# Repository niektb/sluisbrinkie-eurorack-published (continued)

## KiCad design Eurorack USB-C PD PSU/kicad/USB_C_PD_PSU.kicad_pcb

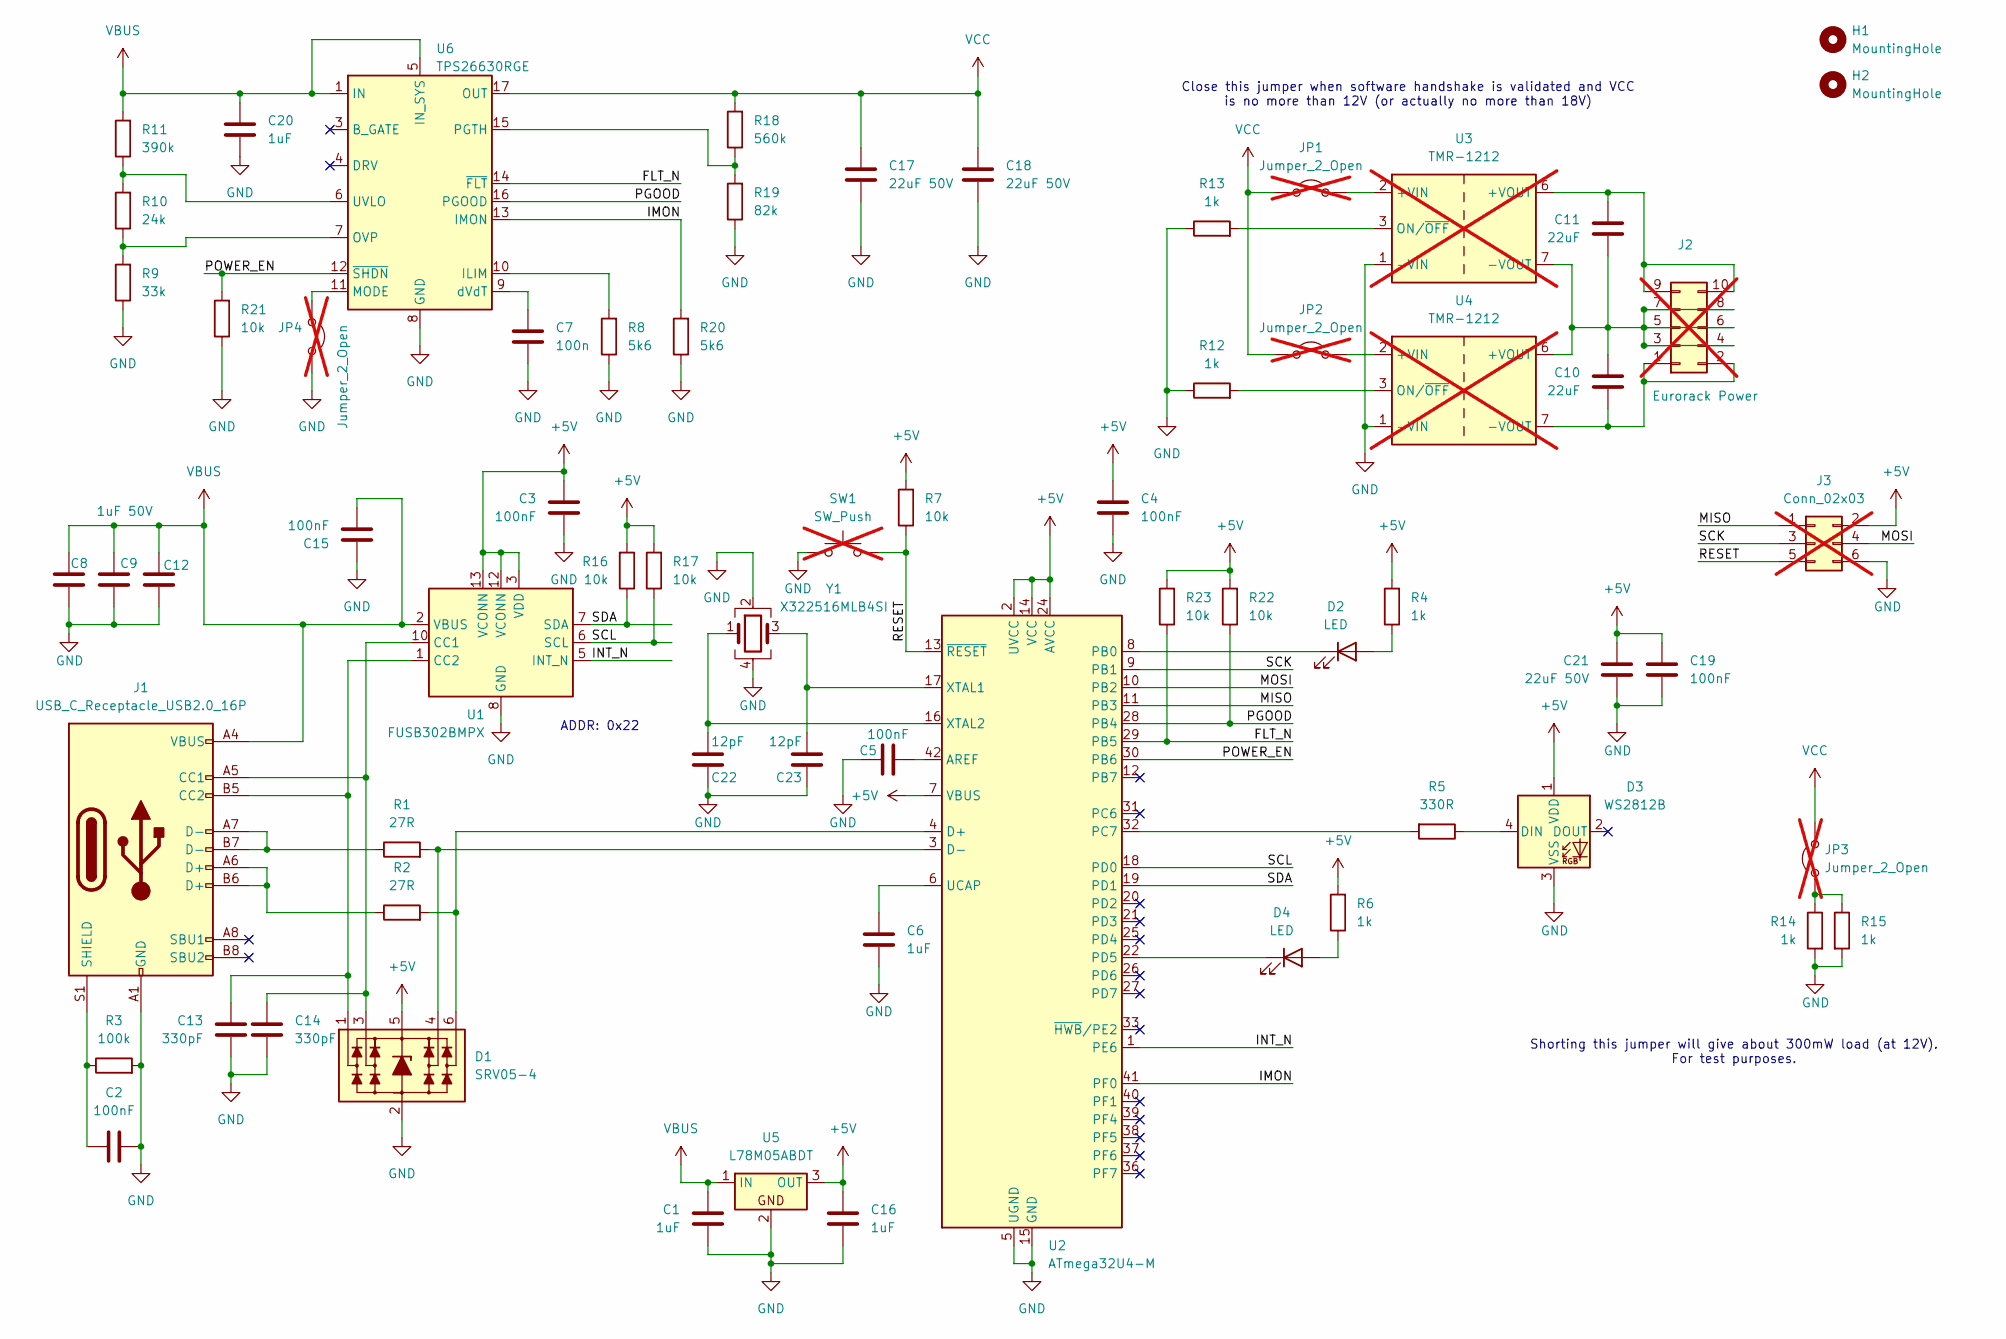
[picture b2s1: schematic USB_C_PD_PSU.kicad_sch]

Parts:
C1, C6, C16, C20: 1uF; C_0603_1608Metric
C2, C3, C4, C5, C15, C19: 100nF; C_0603_1608Metric
C7: 100n; C_0603_1608Metric
C8, C9, C12: 1uF 50V; C_1206_3216Metric
C10, C11: 22uF; C_1206_3216Metric_Pad1.33x1.80mm_HandSolder
C13, C14: 330pF; C_0603_1608Metric
C17, C18, C21: 22uF 50V; C_1206_3216Metric
C22, C23: 12pF; C_0603_1608Metric
D1: SRV05-4; SOT-23-6
D2, D4: LED; LED_0603_1608Metric
D3: WS2812B; LED_WS2812B_PLCC4_5.0x5.0mm_P3.2mm
H1, H2: MountingHole; MountingHole_3.2mm_M3
J1: USB_C_Receptacle_USB2.0_16P; USB_C_Receptacle_G-Switch_GT-USB-7010ASV
J2: Eurorack Power; IDC-Header_2x05_P2.54mm_Vertical; not fitted
J3: Conn_02x03; PinHeader_2x03_P2.54mm_Vertical; Part Number LL1009-2A, 2.54MM 2*3PIN HEADER,LENGTH=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; not fitted
JP1, JP2, JP3, JP4: Jumper_2_Open; JUMPER_SMD_1x2_tiny; not fitted
R1, R2: 27R; R_0603_1608Metric
R3: 100k; R_0603_1608Metric
R4, R6, R12, R13: 1k; R_0603_1608Metric
R5: 330R; R_0603_1608Metric
R7, R16, R17, R21, R22, R23: 10k; R_0603_1608Metric
R8, R20: 5k6; R_0603_1608Metric
R9: 33k; R_0603_1608Metric
R10: 24k; R_0603_1608Metric
R11: 390k; R_0603_1608Metric
R14, R15: 1k; R_1206_3216Metric
R18: 560k; R_0603_1608Metric
R19: 82k; R_0603_1608Metric
SW1: SW_Push; SW_PUSH_6mm; not fitted
U1: FUSB302BMPX; WQFN-14-1EP_2.5x2.5mm_P0.5mm_EP1.45x1.45mm
U2: ATmega32U4-M; QFN-44-1EP_7x7mm_P0.5mm_EP5.2x5.2mm
U3, U4: TMR-1212; Converter_DCDC_TRACO_TMR-xxxx_THT; not fitted
U5: L78M05ABDT; TO-252-2
U6: TPS26630RGE; Texas_RGE0024H_VQFN-24-1EP_4x4mm_P0.5mm_EP2.7x2.7mm
Y1: X322516MLB4SI; Crystal_SMD_3225-4Pin_3.2x2.5mm

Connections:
+5V: C3.1, C4.1, C16.1, C19.1, C21.1, D1.5 (VP), D3.1 (VDD), J3.2 (+12V), R4.2, R6.2, R7.2, R16.2, R17.2, R22.2, R23.2, U1.3 (VDD), U1.4 (VDD), U1.12 (VCONN), U1.13 (VCONN), U2.2 (UVCC), U2.7 (VBUS), U2.14 (VCC), U2.24 (AVCC), U2.34 (VCC), U2.44 (AVCC), U5.3 (OUT)
/FLT_N: R23.1, U2.29 (PB5), U6.14 (~FLT)
/IMON: R20.2, U2.41 (PF0), U6.13 (IMON)
/INT_N: U1.5 (INT_N), U2.1 (PE6)
/MISO: J3.1 (+12V), U2.11 (PB3)
/MOSI: J3.4 (GND), U2.10 (PB2)
/PGOOD: R22.1, U2.28 (PB4), U6.16 (PGOOD)
/POWER_EN: R21.2, U2.30 (PB6), U6.12 (~SHDN)
/RESET: J3.5 (GND), R7.1, SW1.2, U2.13 (~RESET)
/SCK: J3.3 (GND), U2.9 (PB1)
/SCL: R17.1, U1.6 (SCL), U2.18 (PD0)
/SDA: R16.1, U1.7 (SDA), U2.19 (PD1)
GND: C1.2, C2.2, C3.2, C4.2, C5.1, C6.2, C7.2, C8.2, C9.2, C12.2, C13.2, C14.2, C15.1, C16.2, C17.2, C18.2, C19.2, C20.2, C21.2, C22.1, C23.1, D1.2 (VN), D3.3 (VSS), J1.A1 (GND), J1.A12 (GND), J1.B1 (GND), J1.B12 (GND), J3.6 (GND), JP4.1 (A), R3.2, R8.1, R9.1, R12.1, R13.1, R14.2, R15.2, R19.1, R20.1, R21.1, SW1.1, U1.8 (GND), U1.9 (GND), U1.15 (GND), U2.5 (UGND), U2.15 (GND), U2.23 (GND), U2.35 (GND), U2.43 (GND), U2.45 (GND), U3.1 (-VIN), U4.1 (-VIN), U5.2, U6.8 (GND), U6.25 (GND), Y1.2, Y1.4
unnamed: C13.1, D1.1 (L1), J1.B5 (CC2), U1.1 (CC2), U1.14 (CC2)
unnamed: C14.1, D1.3 (L2), J1.A5 (CC1), U1.10 (CC1), U1.11 (CC1)
unnamed: D1.4 (L3), R1.2, U2.3 (D-)
unnamed: D1.6 (L4), R2.2, U2.4 (D+)
unnamed: D2.2 (A), R4.1
unnamed: D2.1 (K), U2.8 (PB0)
unnamed: D3.4 (DIN), R5.1
unnamed: D4.2 (A), R6.1
unnamed: D4.1 (K), U2.22 (PD5)
unnamed: J1.A6 (D+), J1.B6 (D+), R2.1
unnamed: J1.A7 (D-), J1.B7 (D-), R1.1
unnamed: C2.1, J1.S1 (SHIELD), R3.1
unnamed: C10.2, J2.1, J2.2, U4.7 (-VOUT)
unnamed: C10.1, C11.2, J2.3, J2.4, J2.5, J2.6, J2.7, J2.8, U3.7 (-VOUT), U4.6 (+VOUT)
unnamed: C11.1, J2.9, J2.10, U3.6 (+VOUT)
unnamed: JP1.2 (B), U3.2 (+VIN)
unnamed: JP2.2 (B), U4.2 (+VIN)
unnamed: JP3.1 (A), R14.1, R15.1
unnamed: JP4.2 (B), U6.11 (MODE)
unnamed: C5.2, U2.42 (AREF)
unnamed: R5.2, U2.32 (PC7)
unnamed: C6.1, U2.6 (UCAP)
unnamed: C23.2, U2.17 (XTAL1), Y1.3
unnamed: C22.2, U2.16 (XTAL2), Y1.1
unnamed: R13.2, U3.3 (ON/~OFF)
unnamed: R12.2, U4.3 (ON/~OFF)
unnamed: R8.2, U6.10 (ILIM)
unnamed: R9.2, R10.1, U6.7 (OVP)
unnamed: R18.1, R19.2, U6.15 (PGTH)
unnamed: R10.2, R11.1, U6.6 (UVLO)
unnamed: C7.1, U6.9 (dVdT)
VBUS: C1.1, C8.1, C9.1, C12.1, C15.2, C20.1, J1.A4 (VBUS), J1.A9 (VBUS), J1.B4 (VBUS), J1.B9 (VBUS), R11.2, U1.2 (VBUS), U5.1 (IN), U6.1 (IN), U6.2 (IN), U6.5 (IN_SYS)
VCC: C17.1, C18.1, JP1.1 (A), JP2.1 (A), JP3.2 (B), R18.2, U6.17 (OUT), U6.18 (OUT)

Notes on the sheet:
Close this jumper when software handshake is validated and VCC is no more than 12V (or actually no more than 18V)
Shorting this jumper will give about 300mW load (at 12V). For test purposes.
ADDR: 0x22

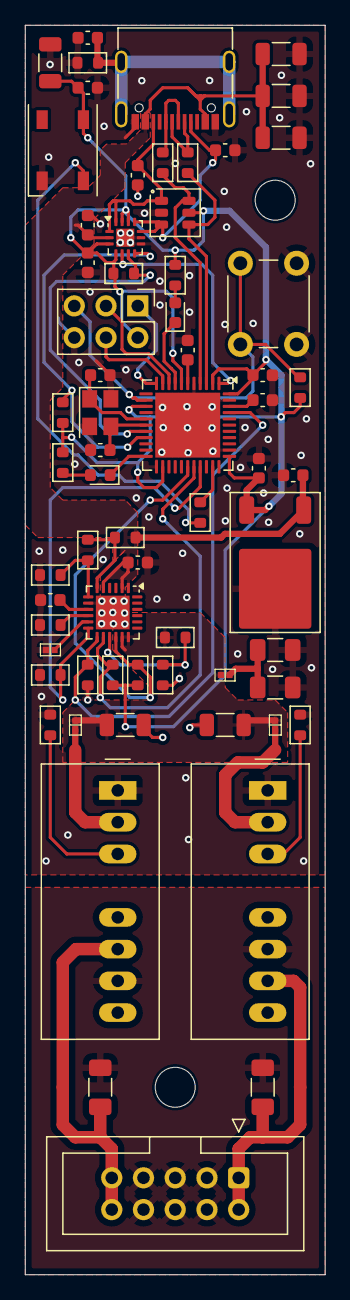
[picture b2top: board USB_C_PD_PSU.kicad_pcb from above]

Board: 2 copper layers, 24.0 x 100.0 mm, 67 parts (0 on the bottom side), 46 nets.

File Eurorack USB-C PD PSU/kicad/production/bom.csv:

Designator,Footprint,Quantity,Value,LCSC Part #
"C1, C16, C20, C6",0603,4,1uF,
"C10, C11",1206,2,22uF,
"C12, C8, C9",1206,3,1uF 50V,
"C13, C14",0603,2,330pF,
"C15, C19, C2, C3, C4, C5",0603,6,100nF,
"C17, C18, C21",1206,3,22uF 50V,
"C22, C23",0603,2,12pF,
C7,0603,1,100n,
D1,SOT-23-6,1,SRV05-4,
"D2, D4",0603,2,LED,
D3,LED_WS2812B_PLCC4_5.0x5.0mm_P3.2mm,1,WS2812B,
J1,USB_C_Receptacle_G-Switch_GT-USB-7010ASV,1,USB_C_Receptacle_USB2.0_16P,
"R1, R2",0603,2,27R,
R10,0603,1,24k,
R11,0603,1,390k,
"R12, R13, R4, R6",0603,4,1k,
"R14, R15",1206,2,1k,
"R16, R17, R21, R22, R23, R7",0603,6,10k,
R18,0603,1,560k,
R19,0603,1,82k,
"R20, R8",0603,2,5k6,
R3,0603,1,100k,
R5,0603,1,330R,
R9,0603,1,33k,
U1,WQFN-14-1EP_2.5x2.5mm_P0.5mm_EP1.45x1.45mm,1,FUSB302BMPX,
U2,QFN-44-1EP_7x7mm_P0.5mm_EP5.2x5.2mm,1,ATmega32U4-M,
U5,TO-252-2,1,L78M05ABDT,
U6,Texas_RGE0024H_VQFN-24-1EP_4x4mm_P0.5mm_EP2.7x2.7mm,1,TPS26630RGE,
Y1,Crystal_SMD_3225-4Pin_3.2x2.5mm,1,X322516MLB4SI,
